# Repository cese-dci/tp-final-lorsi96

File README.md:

## Trabajo práctico final de la asignatura DCI ##
Este repositorio contiene el trabajo práctico final para la asignatura de Diseño de Circuitos Impresos de la carrera de posgrado de FIUBA.

* Autor: Lucas Orsi
* Título corto del trabajo:  Adafruit Power Boost 500
* Descripción: Módulo convertidor elevador de DC-DC que puede funcionar con baterías de 1.8V o más, y convertir ese voltaje a 5.2V DC para proyectos de 5V.

## Resultados Obtenidos

## Estructura del TP FINAL ##

* doc: Toda la información sobre el circuito, principalmente de autoría o procesamiento propio. Por ejemplo:
  * Notas de ingeniería propias.
  * Notas de aplicación propias.
  * Estudios previos, estado del arte, resumen de las investigaciones.
  * Notas con cálculos.
  * Dibujos adicionales.
  * Fotos de los prototipos.
  * Presupuestos, cotizaciones.
* info: Toda la iformación recolectada, principalmente de terceros, como por ejemplo:
  * Hojas de datos.
  * Notas de aplicación.
  * Info de productos comerciales.
  * Info en internet.
* pcb: Archivos de diseño esquemático y pcb.

## Licencia de este trabajo ##
Creative Commons Attribution-ShareAlike 4.0 International

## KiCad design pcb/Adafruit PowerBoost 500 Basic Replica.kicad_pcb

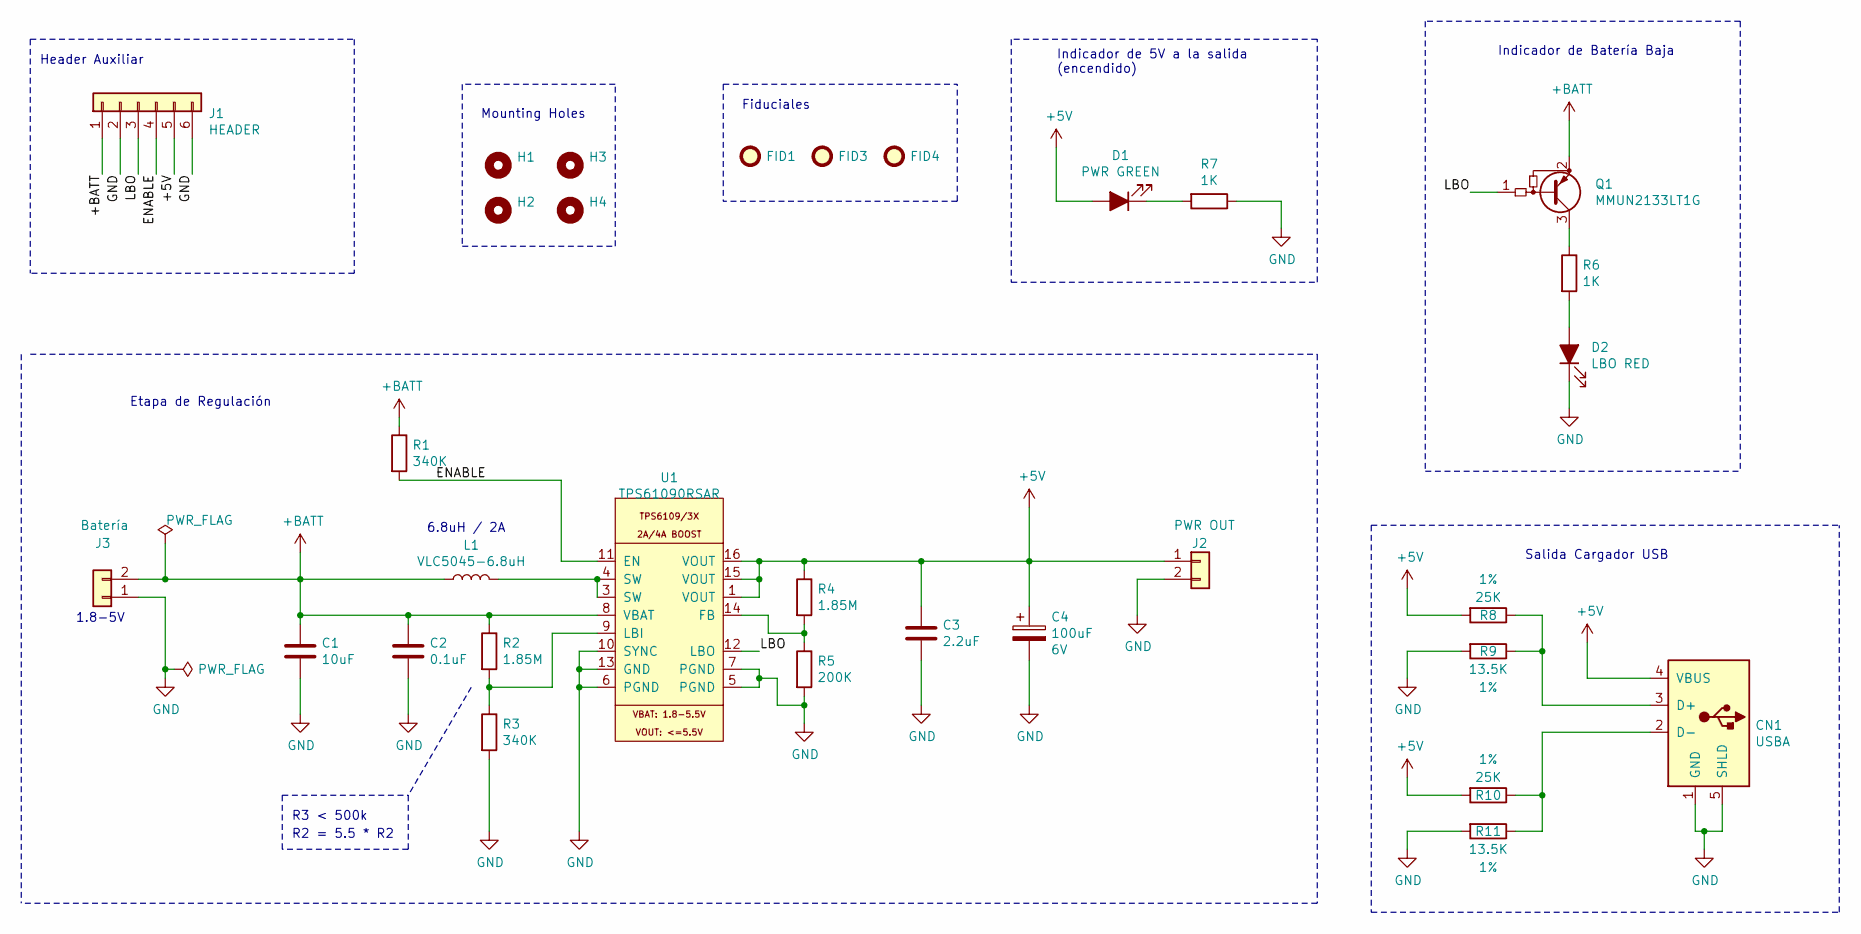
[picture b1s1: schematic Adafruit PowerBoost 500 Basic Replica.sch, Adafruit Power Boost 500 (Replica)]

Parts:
C1: 10uF; C_0805_2012Metric_Pad1.18x1.45mm_HandSolder
C2: 0.1uF; C_0805_2012Metric_Pad1.18x1.45mm_HandSolder
C3: 2.2uF; C_0805_2012Metric_Pad1.18x1.45mm_HandSolder
C4: 100uF; C_1210_3225Metric_Pad1.33x2.70mm_HandSolder; Voltage 6V
CN1: USBA; USB_A_Molex_67643_Horizontal; Mouser N 640-USB1130-15-A
D1: PWR GREEN; LED_0805_2012Metric_Pad1.15x1.40mm_HandSolder
D2: LBO RED; LED_0805_2012Metric_Pad1.15x1.40mm_HandSolder
FID1, FID3, FID4: Fiducial; Fiducial_1mm_Mask2mm
H1, H2: Mounting Hole; MountingHole_3mm
H3, H4: MountingHole; MountingHole_3mm
J1: HEADER; PinSocket_1x06_P1.00mm_Vertical
J2: PWR OUT; JST_EH_S2B-EH_1x02_P2.50mm_Horizontal
J3: Batería; JST_EH_S2B-EH_1x02_P2.50mm_Horizontal
L1: VLC5045-6.8uH; L_Taiyo-Yuden_NR-40xx_HandSoldering; Mouser N 810-VLC5045T-6R8M
Q1: MMUN2133LT1G; SOT-23; Mouser N 863-MMUN2111LT1G
R1, R3: 340K; R_0805_2012Metric_Pad1.20x1.40mm_HandSolder
R2, R4: 1.85M; R_0805_2012Metric_Pad1.20x1.40mm_HandSolder
R5: 200K; R_0805_2012Metric_Pad1.20x1.40mm_HandSolder
R6, R7: 1K; R_0805_2012Metric_Pad1.20x1.40mm_HandSolder
R8, R10: 25K; R_0805_2012Metric_Pad1.20x1.40mm_HandSolder; Tolerance 1%
R9, R11: 13.5K; R_0805_2012Metric_Pad1.20x1.40mm_HandSolder; Tolerance 1%
U1: TPS61090RSAR; QFN-16-1EP_4x4mm_P0.65mm_EP2.1x2.1mm; Mouser N 595-TPS61090RSAR

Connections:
+5V: C3.1, C4.1, CN1.4 (VBUS), D1.2 (A), J1.5, J2.1, R4.1, R8.2, R10.2, U1.1 (VOUT), U1.15 (VOUT), U1.16 (VOUT)
+BATT: C1.1, C2.1, J1.1, J3.2, L1.1, Q1.2 (E), R1.1, R2.1, U1.8 (VBAT)
/ENABLE: J1.4, R1.2, U1.11 (EN)
/LBO: J1.3, Q1.1 (B), U1.12 (LBO)
GND: C1.2, C2.2, C3.2, C4.2, CN1.1 (GND), CN1.5 (SHLD), D2.1 (K), J1.2, J1.6, J2.2, J3.1, R3.2, R5.2, R7.1, R9.2, R11.2, U1.5 (PGND), U1.6 (PGND), U1.7 (PGND), U1.10 (SYNC), U1.13 (GND)
unnamed: CN1.2 (D-), R10.1, R11.1
unnamed: CN1.3 (D+), R8.1, R9.1
unnamed: D1.1 (K), R7.2
unnamed: D2.2 (A), R6.2
unnamed: L1.2, U1.3 (SW), U1.4 (SW)
unnamed: Q1.3 (C), R6.1
unnamed: R2.2, R3.1, U1.9 (LBI)
unnamed: R4.2, R5.1, U1.14 (FB)

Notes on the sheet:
Header Auxiliar
Indicador de 5V a la salida (encendido)
Salida Cargador USB
Indicador de Batería Baja
Mounting Holes
Fiduciales
Etapa de Regulación
1.8-5V
6.8uH / 2A
R3 < 500k
R2 = 5.5 * R2

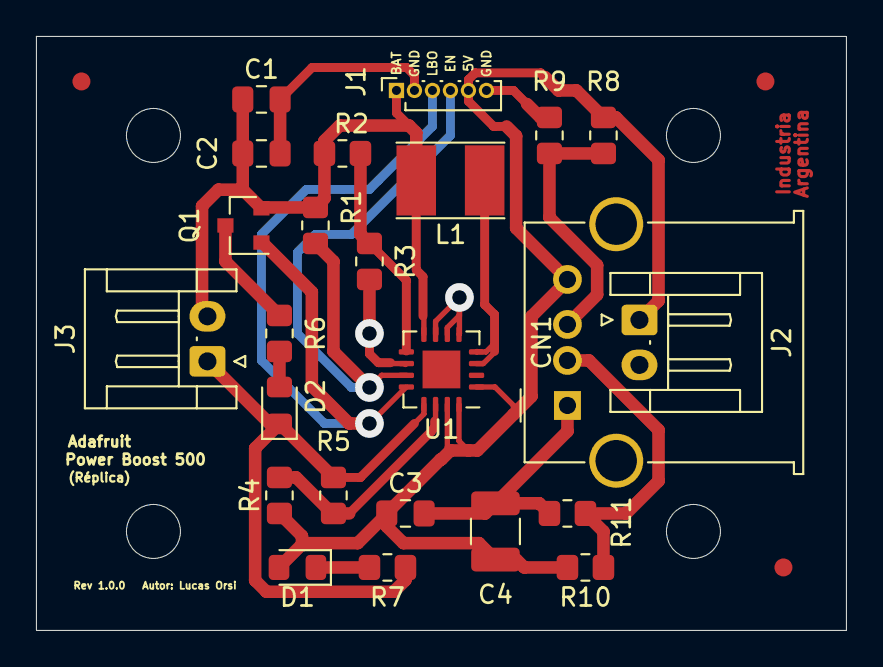
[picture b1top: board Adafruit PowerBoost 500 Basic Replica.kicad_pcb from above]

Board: 2 copper layers, 45.0 x 33.0 mm, 31 parts (0 on the bottom side), 13 nets.

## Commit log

2021-09-09 WIP Schematic
2021-09-18 Agregada la propuesta
2021-09-18 Agregado/s datasheet/s relevantes
2021-09-18 Correcciones de acuerdo a checklist esquematico
2021-09-18 Asignación correcta de pines de U1
2021-09-18 Agrega licencia y actualiza readme
2021-09-23 Posicionamiento tentativo
2021-09-24 Adds missing footprint 3d models
2021-10-03 Agrega Ruteo
2021-10-05 Applies Diego Corrections
2021-10-09 Cambios de acuerdo a checks del excel
2021-10-14 Agrega fotos
2021-10-14 Terminado
2021-10-14 Completa documentacióñ
2021-10-15 Ultimo commit post presentación

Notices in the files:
pcb/Adafruit PowerBoost 500 Basic Replica.kicad_pcb:
Licencia: CC BY 4.0
